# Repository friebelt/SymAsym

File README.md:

# SymAsym
Built of the SymAsym Amp and a bit additional stuff around it

About
I'll build the famous SymAsym Amp itself, mount it in a case and wrap a little Controller and Speaker Protection around it.

Right now the project is a bit of a mess, need to get things togehter and write a proper documentation.

https://www.lf-pro.net/mbittner/Sym5_Webpage/symasym5_3.html
http://sound.whsites.net/project33.htm

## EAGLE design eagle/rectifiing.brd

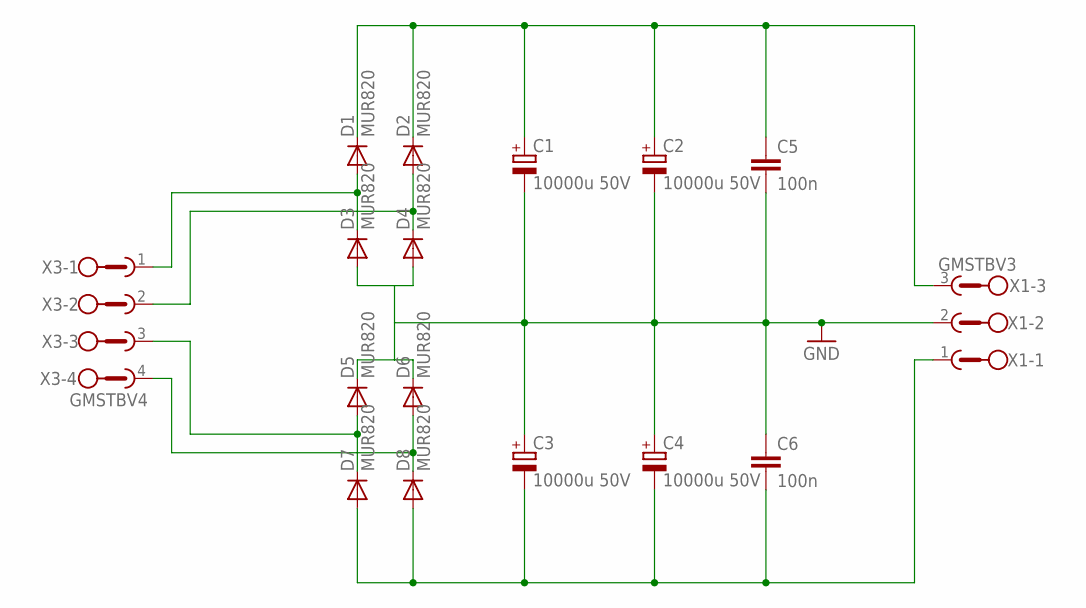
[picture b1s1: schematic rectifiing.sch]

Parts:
C1, C2, C3, C4: 10000u 50V; EB30D
C5, C6: 100n; C075-032X103
D1, D2, D3, D4, D5, D6, D7, D8: MUR820; TO220ACS
X1: GMSTBV3
X3: GMSTBV4

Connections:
GND: C1.-, C2.-, C3.+, C4.+, C5.2, C6.1, D3.A, D4.A, D5.C, D6.C, X1.2
unnamed: C1.+, C2.+, C5.1, D1.C, D2.C, X1.3
unnamed: C3.-, C4.-, C6.2, D7.A, D8.A, X1.1
unnamed: D1.A, D3.C, X3.1
unnamed: D2.A, D4.C, X3.2
unnamed: D6.A, D8.C, X3.4
unnamed: D5.A, D7.C, X3.3

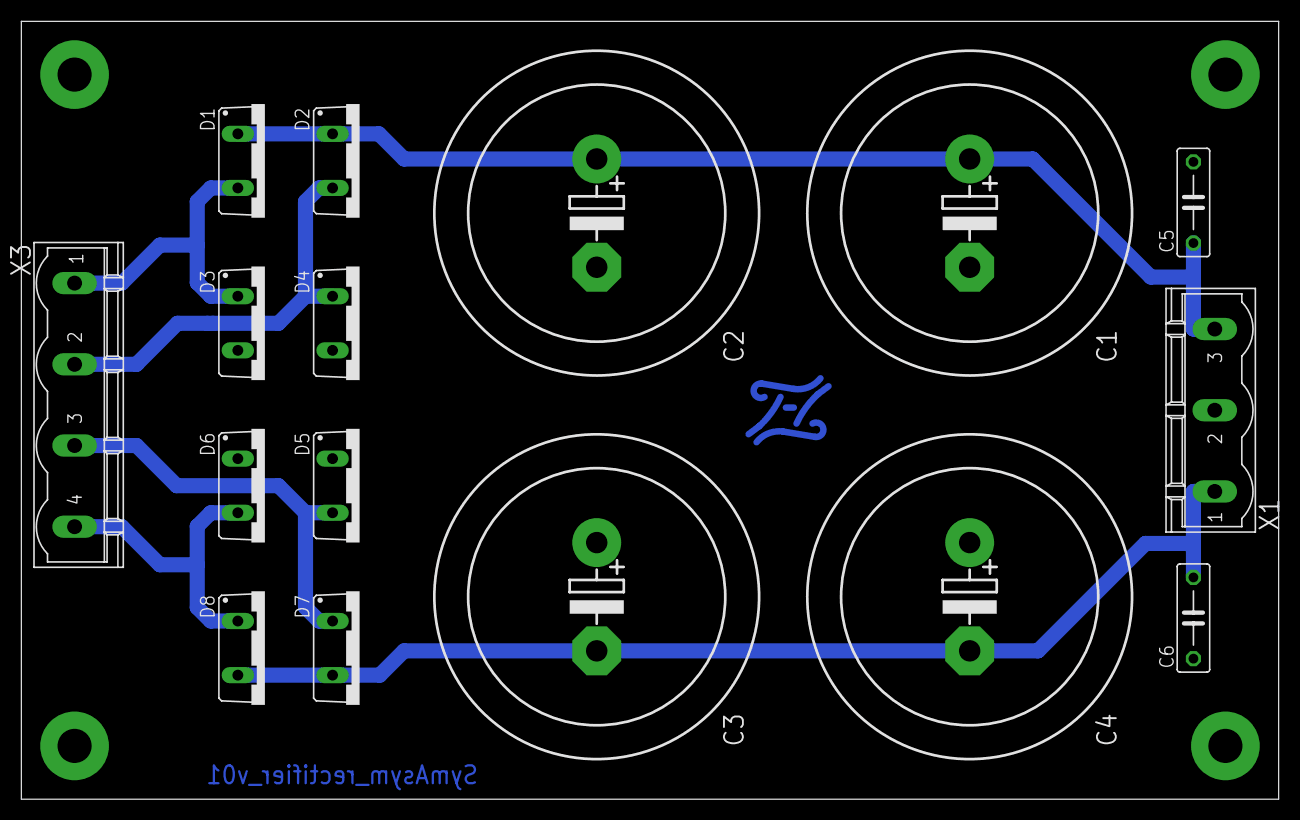
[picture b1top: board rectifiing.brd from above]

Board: 2 copper layers, 118.0 x 73.0 mm, 16 parts (0 on the bottom side), 7 nets.

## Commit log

2018-12-19 first eagle schemes added
2019-01-15 Documentation added
2019-02-18 some early state schematics and CAD files added
2019-02-27 merged some old stuff into docu
2019-03-25 continued working on the CAD model
2019-03-29 continued working on CAD Model, did some PSU calculations
